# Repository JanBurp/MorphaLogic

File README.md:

# MorphaLogic

An Eurorack module based around a Arduino Nano.

With AND, OR, XOR logic functions, a Flip Flip (Q), a Clock Divider mode, and more.

## Inputs, Outputs & Buttons

<table>
<tr>
<td><b>LEFT</b></td><td style="text-align: right;"><b>RIGHT</b></td>
    <tr><td>INPUT: input (A)</td><td style="text-align: right;">OUTPUT: AND (or clock / 16)</td></tr>
    <tr><td>INPUT: input (B)</td><td style="text-align: right;">OUTPUT: OR (or clock / 8)</td></tr>
    <tr><td>INPUT: Inverse (INV)</td><td style="text-align: right;">OUTPUT: XOR (or clock / 4)</td></tr>
    <tr><td>INPUT: Clock (CLK)</td><td style="text-align: right;">OUTPUT: Q - Flip Flop (or clock / 2)</td></tr>
    <tr><td>OUTPUT: Inverse of TRIG BUTTON</td><td style="text-align: right;">Trigger on press & release of TRIG BUTTON</td></tr>
    <tr><td>BUTTON: Mode button</td><td style="text-align: right;">BUTTON: Reset button</td></tr>
    <tr><td colspan="2" style="text-align: center;">TRIG BUTTON</td></tr>
</tr>
</table>

## Functions

### Logic functions

- Basic logic funcions AND, OR, XOR (using the first inputs on the left side).
- Flip Flop (Q) (first input will SET, second input will RESET).
- NOT input, or MODE button, to inverse all logic outputs (NAND, NOR, NXOR, NQ)
- CLOCK input, when present, all Logic outputs only are HIGH when CLOCK is HIGH
- RESET button to reset Q and CLOCK

### Trig button

When the TRIG button is pressed (and released):

- A LOW gate is send to the first (left) output. It will be HIGH when the button is not pressed.
- A short pulse is send to the second output on press & release of the button.
- If the module is in Clock Divider mode, the press & release time will set the Clock Tempe if no signal is present on the CLOCK input.

## Modes:

Current mode is set in memory.

### Normal mode (mode button is unlit):

- Inputs A & B determines logic outputs (AND, OR, XOR, Q). Where A is set and B is reset for the flipflop (Q).
- If the NOT input is HIGH, all logic outputs are inverted (NAND, NOR, NXOR,NQ)

### Inverse mode (mode button is lit):

- Pressing the mode button will inverse all logic outputs (same as when NOT input is HIGH)

### Clockdivider mode (mode button is flashing):

- A long press on the mode button will put the module in Clockdivider mode. The mode button will flash.
- The logic outputs will divide the clock (where Q = /2, XOR = /4, OR = /8, AND =/16)
- The clock source is:
  - The CLK input
  - If no clock is present on the CLK input, a standard 120 BPM clock is used.
  - Or, if the trig buttons has been pressed and released, the timing between press and release is used to determine the clock time.

### External Trig Mode (trig button flashes):

- A long press of the RESET button toggles between external trig options mode on/off. When on, the trig button flashes.
- When external trig mode is on, the first input can function as an external trig for the trig button.

## Uses

- Use the logic function for all kinds of GATE manipluations, for interesting sequences for example.
- Same for the CLOCK DIVIDER mode.
- Make use of the CLOCK input to quantize the logic outputs with a clock signal.
- Use the TRIG BUTTON (or external trig mode) for changing a GATE into two short TRIGS.
- Use the TRIG BUTTON to fire a LOW gate (patch it into one of the logic function to have a HIGH gate on the OR output).

### Example with a Morphagene

One of my main modules in my eurorack case is the Make-Noise Morphagene. One thing that i'd like it to do is:

- Press and hold button to record - currently playing loop is stopped, and recording is started.
- Release button - recording is stopped and starts playing.

To make this work:

- Prepare the Morphagene by setting the `Record option (rsop)` in the `options.txt` file on the SD card to '1'.
- Patch the TRIGGER output of the TRIG BUTTON to the RECORD input of the Morphagene
- Patch the INVERSE output of the TRIG BUTTOON to the PLAY input of the Morphagene

Now:

- When pressing (and holding) the TRIG BUTTON the Morphagene start recording (and stops playing).
- When releasing the TRIG BUTTON the Morphagene stops recording and starts playing.
- If in Clock Divider mode and no Clock signal is present at the CLOCK input, the tempo is set to the time between pressing and releasing the button.

# Content:

In this repo you'll find:

- Arduino program
- Schematics
- BOM
- KiCad project with schematics & PCB & FrontPanel PCB
- STL file for printing the buttons
- Several pictures

# Buying a kit

If you'd like to build this module you can buy a kit with:

- PCB
- Frontpanel
- 3D printed buttons

Contact me if you are interested.

By Jan den Besten <a href="https://www.jandenbesten.com">www.jandenbesten.com</a>

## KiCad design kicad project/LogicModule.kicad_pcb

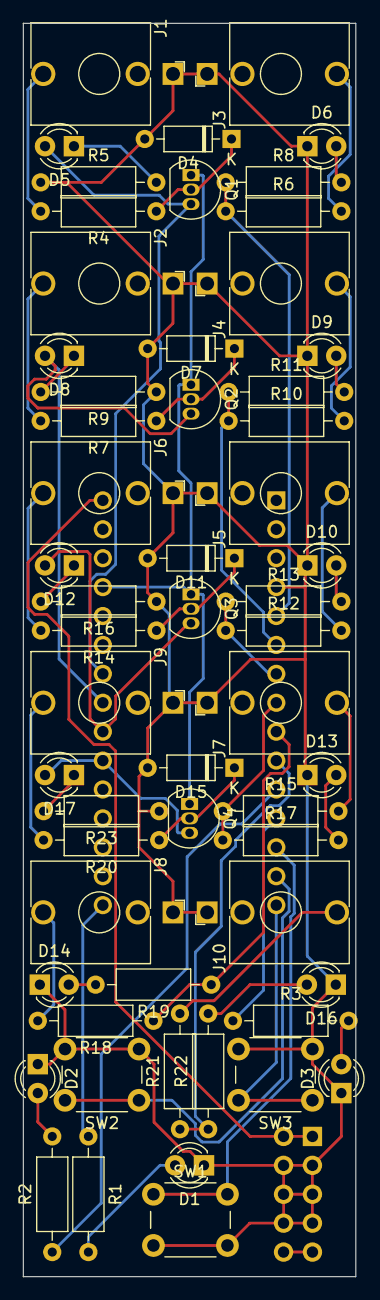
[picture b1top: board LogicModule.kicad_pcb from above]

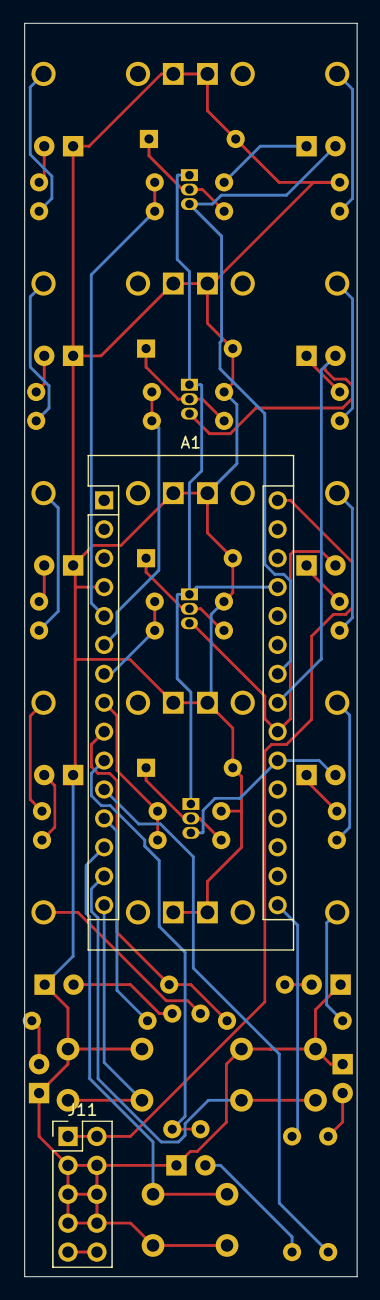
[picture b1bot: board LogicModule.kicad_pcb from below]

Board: 2 copper layers, 29.2 x 110.1 mm, 59 parts (2 on the bottom side), 47 nets.

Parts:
A1: Arduino_Nano_v2.x; Arduino_Nano
D1: LED button; LED_D3.0mm
D2: LED Mode; LED_D3.0mm
D3: LED Reset; LED_D3.0mm
D4, D7, D11, D15: 1N4148; D_DO-35_SOD27_P7.62mm_Horizontal
D5: LED inpA; LED_D3.0mm
D6: LED AND; LED_D3.0mm
D8: LED inpB; LED_D3.0mm
D9: LED OR; LED_D3.0mm
D10: LED XOR; LED_D3.0mm
D12: LED inpNOT; LED_D3.0mm
D13: LED Q; LED_D3.0mm
D14: LED ngate; LED_D3.0mm
D16: LED trig; LED_D3.0mm
D17: LED inpCLK; LED_D3.0mm
J1: INPUT A; Jack_3.5mm_QingPu_WQP-PJ398SM_Vertical_CircularHoles
J2: INPUT B; Jack_3.5mm_QingPu_WQP-PJ398SM_Vertical_CircularHoles
J3: AND; Jack_3.5mm_QingPu_WQP-PJ398SM_Vertical_CircularHoles
J4: OR; Jack_3.5mm_QingPu_WQP-PJ398SM_Vertical_CircularHoles
J5: XOR; Jack_3.5mm_QingPu_WQP-PJ398SM_Vertical_CircularHoles
J6: INPUT NOT; Jack_3.5mm_QingPu_WQP-PJ398SM_Vertical_CircularHoles
J7: Q; Jack_3.5mm_QingPu_WQP-PJ398SM_Vertical_CircularHoles
J8: NGATE; Jack_3.5mm_QingPu_WQP-PJ398SM_Vertical_CircularHoles
J9: INPUT CLOCK; Jack_3.5mm_QingPu_WQP-PJ398SM_Vertical_CircularHoles
J10: TRIG; Jack_3.5mm_QingPu_WQP-PJ398SM_Vertical_CircularHoles
J11: Conn_02x05_Odd_Even; PinHeader_2x05_P2.54mm_Vertical
Q1, Q2, Q3, Q4: BC337; TO-92_Inline
R1, R2, R3, R5, R9, R16, R23: 1k; R_Axial_DIN0207_L6.3mm_D2.5mm_P10.16mm_Horizontal
R4, R7, R14, R20: 10k; R_Axial_DIN0207_L6.3mm_D2.5mm_P10.16mm_Horizontal
R6, R8, R10, R11, R12, R13, R15, R17, R18, R19, R21, R22: 1K; R_Axial_DIN0207_L6.3mm_D2.5mm_P10.16mm_Horizontal
SW1: Button; SW_PUSH_6mm
SW2: Mode; SW_PUSH_6mm
SW3: Reset; SW_PUSH_6mm

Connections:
+12V: A1.30, J11.1, J11.2
GND: A1.4, D1.1, D2.1, D3.1, D4.2, D6.1, D7.2, D9.1, D10.1, D11.2, D13.1, D14.1, D15.2, D16.1, J1.S, J2.S, J3.S, J4.S, J5.S, J6.S, J7.S, J8.S, J9.S, J10.S, J11.3, J11.4, J11.5, J11.6, J11.7, J11.8, R5.1, R9.1, R16.1, R23.1, SW1.2, SW2.2, SW3.2
unnamed: A1.5, R6.1, R8.1
unnamed: A1.6, R10.1, R11.1
unnamed: A1.7, R12.1, R13.1
unnamed: A1.8, R15.1, R17.1
unnamed: A1.9, R18.1, R19.1
unnamed: A1.10, R21.1, R22.1
unnamed: A1.11, R2.1
unnamed: A1.12, R3.1
unnamed: A1.13, SW1.1
unnamed: A1.14, SW2.1
unnamed: A1.15, SW3.1
unnamed: A1.16, R1.1
unnamed: A1.21, D17.2, Q4.3
unnamed: A1.22, D12.2, Q3.3
unnamed: A1.23, D8.2, Q2.3
unnamed: A1.24, D5.2, Q1.3
unnamed: A1.27, Q1.1, Q2.1, Q3.1, Q4.1
unnamed: D1.2, R1.2
unnamed: D2.2, R2.2
unnamed: D3.2, R3.2
unnamed: D4.1, Q1.2, R4.1
unnamed: D5.1, R5.2
unnamed: D6.2, R8.2
unnamed: D7.1, Q2.2, R7.1
unnamed: D8.1, R9.2
unnamed: D9.2, R11.2
unnamed: D10.2, R13.2
unnamed: D11.1, Q3.2, R14.1
unnamed: D12.1, R16.2
unnamed: D13.2, R17.2
unnamed: D14.2, R19.2
unnamed: D15.1, Q4.2, R20.1
unnamed: D16.2, R22.2
unnamed: D17.1, R23.2
unnamed: J1.T, R4.2
unnamed: J2.T, R7.2
unnamed: J3.T, R6.2
unnamed: J4.T, R10.2
unnamed: J5.T, R12.2
unnamed: J6.T, R14.2
unnamed: J7.T, R15.2
unnamed: J8.T, R18.2
unnamed: J9.T, R20.2
unnamed: J10.T, R21.2
unnamed: J11.9, J11.10

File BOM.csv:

"#","Reference","Qty","Value","Footprint","DNP"
"1","A1","1","Arduino_Nano_v2.x","Module:Arduino_Nano",""
"2","D1","1","LED button","LED_THT:LED_D3.0mm",""
"3","D2","1","LED Mode","LED_THT:LED_D3.0mm",""
"4","D3","1","LED Reset","LED_THT:LED_D3.0mm",""
"5","D4, D7, D11, D15","4","1N4148","Diode_THT:D_DO-35_SOD27_P7.62mm_Horizontal",""
"6","D5","1","LED inpA","LED_THT:LED_D3.0mm",""
"7","D6","1","LED AND ","LED_THT:LED_D3.0mm",""
"8","D8","1","LED inpB","LED_THT:LED_D3.0mm",""
"9","D9","1","LED OR","LED_THT:LED_D3.0mm",""
"10","D10","1","LED XOR","LED_THT:LED_D3.0mm",""
"11","D12","1","LED inpNOT","LED_THT:LED_D3.0mm",""
"12","D13","1","LED Q","LED_THT:LED_D3.0mm",""
"13","D14","1","LED ngate","LED_THT:LED_D3.0mm",""
"14","D16","1","LED trig","LED_THT:LED_D3.0mm",""
"15","D17","1","LED inpCLK","LED_THT:LED_D3.0mm",""
"16","J1","1","INPUT A","Connector_Audio:Jack_3.5mm_QingPu_WQP-PJ398SM_Vertical_CircularHoles",""
"17","J2","1","INPUT B","Connector_Audio:Jack_3.5mm_QingPu_WQP-PJ398SM_Vertical_CircularHoles",""
"18","J3","1","AND","Connector_Audio:Jack_3.5mm_QingPu_WQP-PJ398SM_Vertical_CircularHoles",""
"19","J4","1","OR","Connector_Audio:Jack_3.5mm_QingPu_WQP-PJ398SM_Vertical_CircularHoles",""
"20","J5","1","XOR","Connector_Audio:Jack_3.5mm_QingPu_WQP-PJ398SM_Vertical_CircularHoles",""
"21","J6","1","INPUT NOT","Connector_Audio:Jack_3.5mm_QingPu_WQP-PJ398SM_Vertical_CircularHoles",""
"22","J7","1","Q","Connector_Audio:Jack_3.5mm_QingPu_WQP-PJ398SM_Vertical_CircularHoles",""
"23","J8","1","NGATE","Connector_Audio:Jack_3.5mm_QingPu_WQP-PJ398SM_Vertical_CircularHoles",""
"24","J9","1","INPUT CLOCK","Connector_Audio:Jack_3.5mm_QingPu_WQP-PJ398SM_Vertical_CircularHoles",""
"25","J10","1","TRIG","Connector_Audio:Jack_3.5mm_QingPu_WQP-PJ398SM_Vertical_CircularHoles",""
"26","J11","1","Conn_02x05_Odd_Even","Connector_PinHeader_2.54mm:PinHeader_2x05_P2.54mm_Vertical",""
"27","Q1, Q2, Q3, Q4","4","BC337","Package_TO_SOT_THT:TO-92_Inline",""
"28","R1, R2, R3, R5, R9, R16, R23","7","1k","Resistor_THT:R_Axial_DIN0207_L6.3mm_D2.5mm_P10.16mm_Horizontal",""
"29","R4, R7, R14, R20","4","10k","Resistor_THT:R_Axial_DIN0207_L6.3mm_D2.5mm_P10.16mm_Horizontal",""
"30","R6, R8, R10, R11, R12, R13, R15, R17, R18, R19, R21, R22","12","1K","Resistor_THT:R_Axial_DIN0207_L6.3mm_D2.5mm_P10.16mm_Horizontal",""
"31","SW1","1","Button","Button_Switch_THT:SW_PUSH_6mm",""
"32","SW2","1","Mode","Button_Switch_THT:SW_PUSH_6mm",""
"33","SW3","1","Reset","Button_Switch_THT:SW_PUSH_6mm",""

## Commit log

2021-07-07 commit basics
2023-10-20 Add picture to READ.me
2023-12-19 cleanup
2023-12-19 adding arduino code as submodule
2023-12-19 fix code (not as submodule)
2023-12-19 remove submodule
2023-12-19 Adding code
2023-12-19 added schematic
2023-12-19 Adding BOM & KiCad
2023-12-19 typo
2023-12-19 adding 3D buttons
2023-12-19 pictures
2023-12-19 nicer text
2023-12-19 docs
2023-12-19 pictures for pages
2023-12-19 doc update
